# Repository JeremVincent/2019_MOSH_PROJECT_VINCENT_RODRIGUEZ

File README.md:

README for the SMART Device project

In the current folder, you can retrieve the files for the kicad project. Then, in the arduino folder, there are all the files needed to lunch the arduino project. This program will start our captor and read the value of the gaz
density in the place. If this value is too high to be secure, it sends a notification to the Lora ttn node.

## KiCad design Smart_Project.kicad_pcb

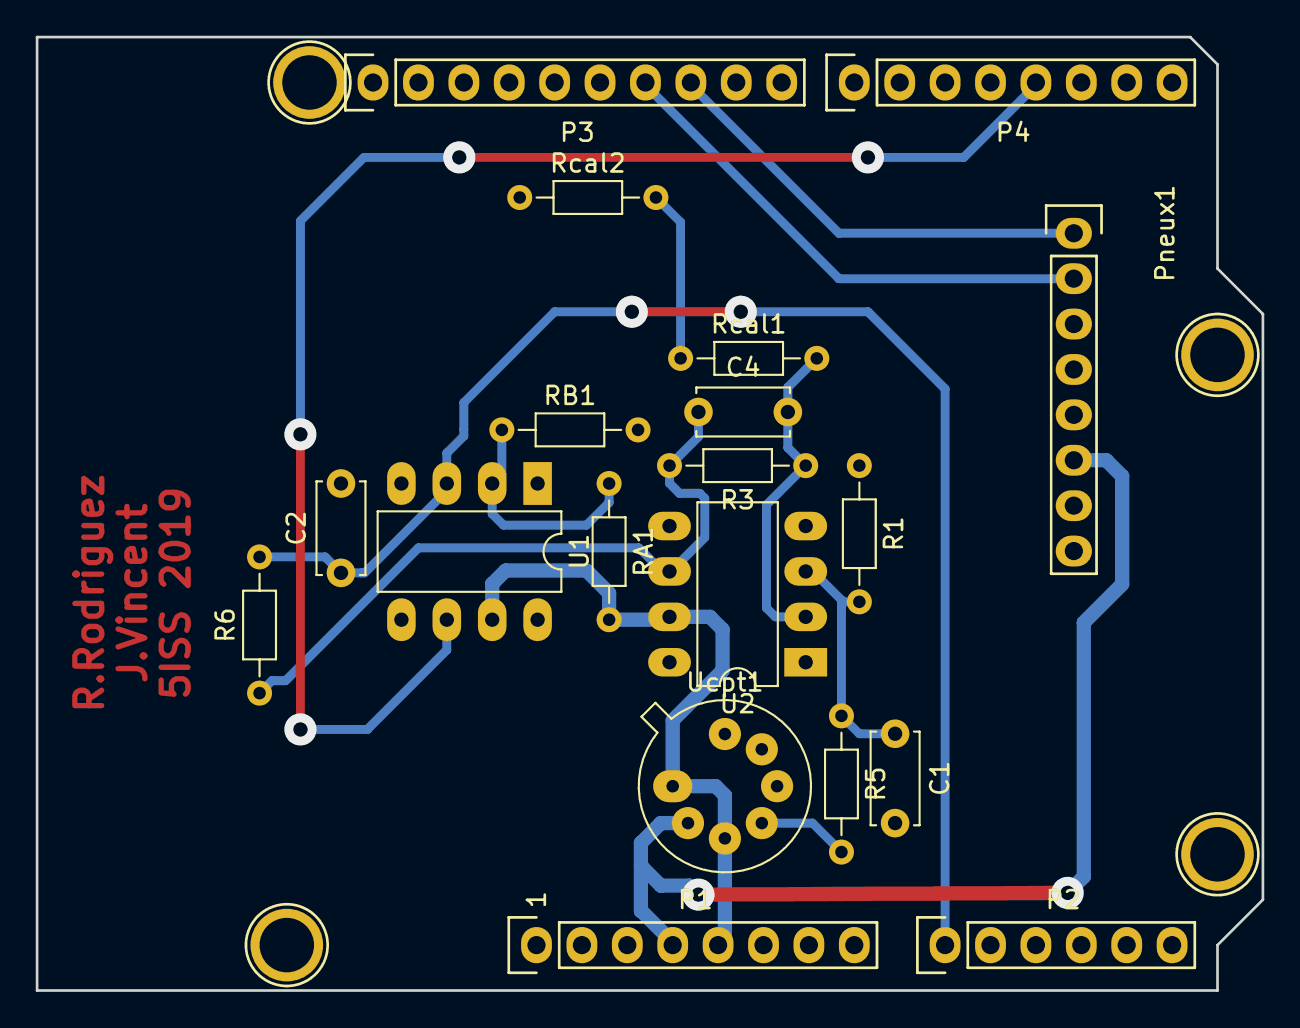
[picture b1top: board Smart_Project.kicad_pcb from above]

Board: 2 copper layers, 68.6 x 53.3 mm, 23 parts (0 on the bottom side), 13 nets.

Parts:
C1, C2, C4: C; C_Disc_D5.0mm_W2.5mm_P5.00mm
P1: Power; Socket_Strip_Arduino_1x08
P2: Analog; Socket_Strip_Arduino_1x06
P3: Digital; Socket_Strip_Arduino_1x10
P4: Digital; Socket_Strip_Arduino_1x08
P5, P6, P7, P8: CONN_01X01; Arduino_1pin
Pneux1: Laura_Adaptator; Socket_Strip_Arduino_1x08
R1, R3, R5, R6: R; R_Axial_DIN0204_L3.6mm_D1.6mm_P7.62mm_Horizontal
RA1: R; R_Axial_DIN0204_L3.6mm_D1.6mm_P7.62mm_Horizontal
RB1: R; R_Axial_DIN0204_L3.6mm_D1.6mm_P7.62mm_Horizontal
Rcal1, Rcal2: R; R_Axial_DIN0204_L3.6mm_D1.6mm_P7.62mm_Horizontal
U1, U2: LTC1050; DIP-8_W7.62mm_LongPads
Ucpt1: T05; TO5

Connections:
+3V3: P1.4, Pneux1.6, Ucpt1.2
+5V: P1.5, RA1.2, U1.7, U2.7, Ucpt1.1, Ucpt1.3
A0: C2.1, P2.1, R6.2, U1.3
Comparateur_Output: P4.5, U1.6
GND: C1.2, C2.2, P1.6, P1.7, P3.4, Pneux1.8, R1.1, RB1.2, Rcal2.1, U1.4, U2.4, Ucpt1.5, Ucpt1.6, Ucpt1.7
unnamed: C1.1, R1.2, R5.1, U2.3
unnamed: C4.1, R3.2, R6.1, U2.6
unnamed: C4.2, R3.1, Rcal1.2, U2.2
unnamed: R5.2, Ucpt1.4
unnamed: RA1.1, RB1.1, U1.2
unnamed: Rcal1.1, Rcal2.2
Rx: P3.7, Pneux1.2
Tx: P3.8, Pneux1.1

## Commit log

2019-12-02 Projet final
2019-12-11 Modification des largeurs de pistes et ajout du plan de masse
2020-01-21 Ajout du projet Arduino
